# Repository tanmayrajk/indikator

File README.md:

# don't hit me (indikator)

## what is it

don't hit me is a project containing multiple tools/gadgets to aid us during biking. atm there's a handle bar with indicator lights in [the repo dont-hit-me](https://github.com/istoocold/dont-hit-me) and an actual indicator for the seat in this repo. 

there's plans for more stuff like phone holder, some sort of communication between bikes and other stuff maybe.

## features

- indicators on the handle bar that will tell you where your partner is moving.
- indicators for the seat that will allow others to see where you are moving.
- buttons on the handle bar to use the indicator lights.
- using espnow to communicate between the handle bar and the indicators AND the bikes.

## repos

it's currently divided between two repos:
- indikator (this repo)
- dont-hit-me ([https://github.com/istoocold/dont-hit-me](https://github.com/istoocold/dont-hit-me))

## installation

there's no installation needed tbh. just close the repo and open it with kicad. same for the dont-hit-me repo. use freecad for the cad stuff.

## ai usage

we just used chatgpt for asking questions. ai was not used for generating any code or images, etc.

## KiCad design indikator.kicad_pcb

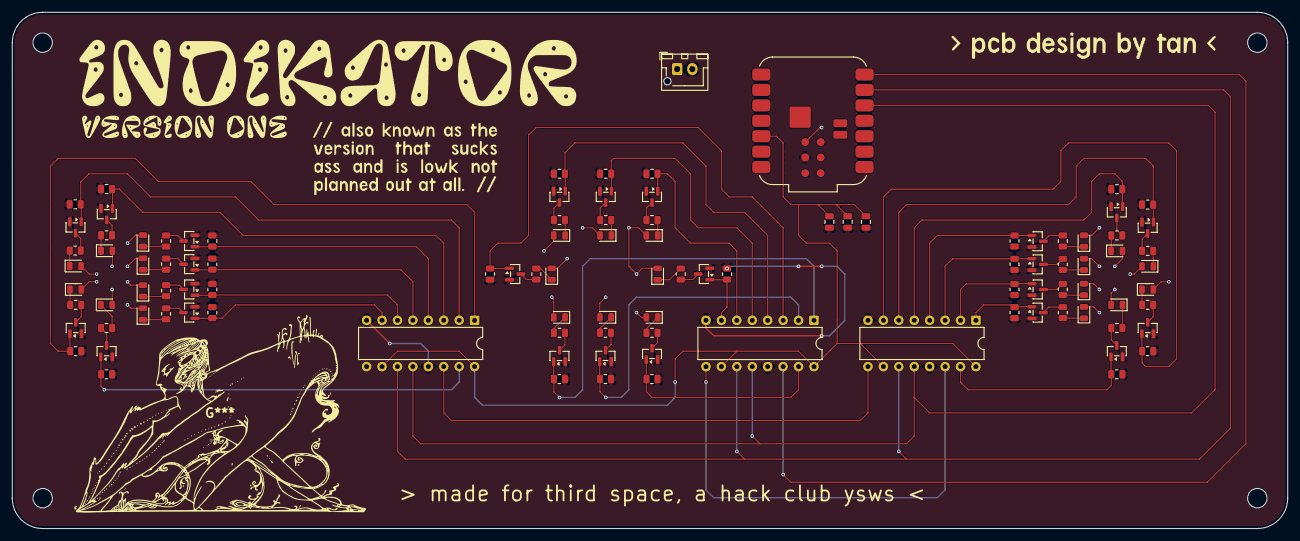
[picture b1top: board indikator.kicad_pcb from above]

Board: 2 copper layers, 210.0 x 85.0 mm, 104 parts (0 on the bottom side), 80 nets.

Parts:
C1, C2, C3: C; C_0805_2012Metric
D1, D2, D3, D4, D5, D6, D7, D8, D9, D10, D11, D12, D13, D14, D15, D16, D17, D18, D19, D20, D21, D22, D23, D24: LED; LED_0805_2012Metric
J1: Conn_01x02; JST_XH_B2B-XH-AM_1x02_P2.50mm_Vertical
Q1, Q2, Q3, Q4, Q5, Q6, Q7, Q8, Q9, Q10, Q11, Q12, Q13, Q14, Q15, Q16, Q17, Q18, Q19, Q20, Q21, Q22, Q23, Q24: AO3400A; SOT-23
R1, R2, R3, R4, R5, R6, R7, R8, R9, R10, R11, R12, R13, R14, R15, R16, R17, R18, R19, R20, R21, R22, R23, R24, R25, R26, R27, R28, R29, R30, R31, R32, R33, R34, R35, R36, R37, R38, R39, R40, R41, R42, R43, R44, R45, R46, R47, R48: R; R_0805_2012Metric
U1: XIAO-ESP32-C3-SMD; MCU_Seeed_ESP32C3
U2, U3, U4: 74HC595; DIP-16_W7.62mm

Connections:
/ESP3V3: C1.1, C2.1, C3.1, U1.12 (3V3_OUT), U2.10 (~SRCLR), U2.16 (VCC), U3.10 (~SRCLR), U3.16 (VCC), U4.10 (~SRCLR), U4.16 (VCC)
/QH'1: U2.9 (QH'), U3.14 (SER)
/QH'2: U3.9 (QH'), U4.14 (SER)
/RCLK: U1.5 (D4), U2.12 (RCLK), U3.12 (RCLK), U4.12 (RCLK)
/SER: U1.7 (D6), U2.14 (SER)
/SRCLK: U1.6 (D5), U2.11 (SRCLK), U3.11 (SRCLK), U4.11 (SRCLK)
/VBAT+: D1.2 (A), D2.2 (A), D3.2 (A), D4.2 (A), D5.2 (A), D6.2 (A), D7.2 (A), D8.2 (A), D9.2 (A), D10.2 (A), D11.2 (A), D12.2 (A), D13.2 (A), D14.2 (A), D15.2 (A), D16.2 (A), D17.2 (A), D18.2 (A), D19.2 (A), D20.2 (A), D21.2 (A), D22.2 (A), D23.2 (A), D24.2 (A), J1.1, U1.21 (VBAT)
GND: C1.2, C2.2, C3.2, J1.2, Q1.2 (S), Q2.2 (S), Q3.2 (S), Q4.2 (S), Q5.2 (S), Q6.2 (S), Q7.2 (S), Q8.2 (S), Q9.2 (S), Q10.2 (S), Q11.2 (S), Q12.2 (S), Q13.2 (S), Q14.2 (S), Q15.2 (S), Q16.2 (S), Q17.2 (S), Q18.2 (S), Q19.2 (S), Q20.2 (S), Q21.2 (S), Q22.2 (S), Q23.2 (S), Q24.2 (S), R1.2, R3.2, R5.2, R6.2, R7.2, R8.2, R9.2, R10.2, R17.2, R18.2, R19.2, R20.2, R21.2, R22.2, R23.2, R24.2, R33.2, R34.2, R35.2, R36.2, R37.2, R38.2, R39.2, R40.2, U1.22 (GND), U2.8 (GND), U2.13 (~OE), U3.8 (GND), U3.13 (~OE), U4.8 (GND), U4.13 (~OE)
unnamed: D1.1 (K), R2.2
unnamed: D2.1 (K), R4.2
unnamed: D3.1 (K), R11.2
unnamed: D4.1 (K), R12.2
unnamed: D5.1 (K), R13.2
unnamed: D6.1 (K), R14.2
unnamed: D7.1 (K), R15.2
unnamed: D8.1 (K), R16.2
unnamed: D9.1 (K), R25.2
unnamed: D10.1 (K), R26.2
unnamed: D11.1 (K), R27.2
unnamed: D12.1 (K), R28.2
unnamed: D13.1 (K), R29.2
unnamed: D14.1 (K), R30.2
unnamed: D15.1 (K), R31.2
unnamed: D16.1 (K), R32.2
unnamed: D17.1 (K), R41.2
unnamed: D18.1 (K), R42.2
unnamed: D19.1 (K), R43.2
unnamed: D20.1 (K), R44.2
unnamed: D21.1 (K), R45.2
unnamed: D22.1 (K), R46.2
unnamed: D23.1 (K), R47.2
unnamed: D24.1 (K), R48.2
unnamed: Q1.3 (D), R2.1
unnamed: Q1.1 (G), R1.1, U2.15 (QA)
unnamed: Q2.3 (D), R4.1
unnamed: Q2.1 (G), R3.1, U2.1 (QB)
unnamed: Q3.3 (D), R11.1
unnamed: Q3.1 (G), R5.1, U2.2 (QC)
unnamed: Q4.3 (D), R12.1
unnamed: Q4.1 (G), R6.1, U2.3 (QD)
unnamed: Q5.3 (D), R13.1
unnamed: Q5.1 (G), R7.1, U2.4 (QE)
unnamed: Q6.3 (D), R14.1
unnamed: Q6.1 (G), R8.1, U2.5 (QF)
unnamed: Q7.3 (D), R15.1
unnamed: Q7.1 (G), R9.1, U2.6 (QG)
unnamed: Q8.3 (D), R16.1
unnamed: Q8.1 (G), R10.1, U2.7 (QH)
unnamed: Q9.3 (D), R25.1
unnamed: Q9.1 (G), R17.1, U3.15 (QA)
unnamed: Q10.3 (D), R26.1
unnamed: Q10.1 (G), R18.1, U3.1 (QB)
unnamed: Q11.3 (D), R27.1
unnamed: Q11.1 (G), R19.1, U3.2 (QC)
unnamed: Q12.3 (D), R28.1
unnamed: Q12.1 (G), R20.1, U3.3 (QD)
unnamed: Q13.3 (D), R29.1
unnamed: Q13.1 (G), R21.1, U3.4 (QE)
unnamed: Q14.3 (D), R30.1
unnamed: Q14.1 (G), R22.1, U3.5 (QF)
unnamed: Q15.3 (D), R31.1
unnamed: Q15.1 (G), R23.1, U3.6 (QG)
unnamed: Q16.3 (D), R32.1
unnamed: Q16.1 (G), R24.1, U3.7 (QH)
unnamed: Q17.3 (D), R41.1
unnamed: Q17.1 (G), R33.1, U4.15 (QA)
unnamed: Q18.3 (D), R42.1
unnamed: Q18.1 (G), R34.1, U4.1 (QB)
unnamed: Q19.3 (D), R43.1
unnamed: Q19.1 (G), R35.1, U4.2 (QC)
unnamed: Q20.3 (D), R44.1
unnamed: Q20.1 (G), R36.1, U4.3 (QD)
unnamed: Q21.3 (D), R45.1
unnamed: Q21.1 (G), R37.1, U4.4 (QE)
unnamed: Q22.3 (D), R46.1
unnamed: Q22.1 (G), R38.1, U4.5 (QF)
unnamed: Q23.3 (D), R47.1
unnamed: Q23.1 (G), R39.1, U4.6 (QG)
unnamed: Q24.3 (D), R48.1
unnamed: Q24.1 (G), R40.1, U4.7 (QH)

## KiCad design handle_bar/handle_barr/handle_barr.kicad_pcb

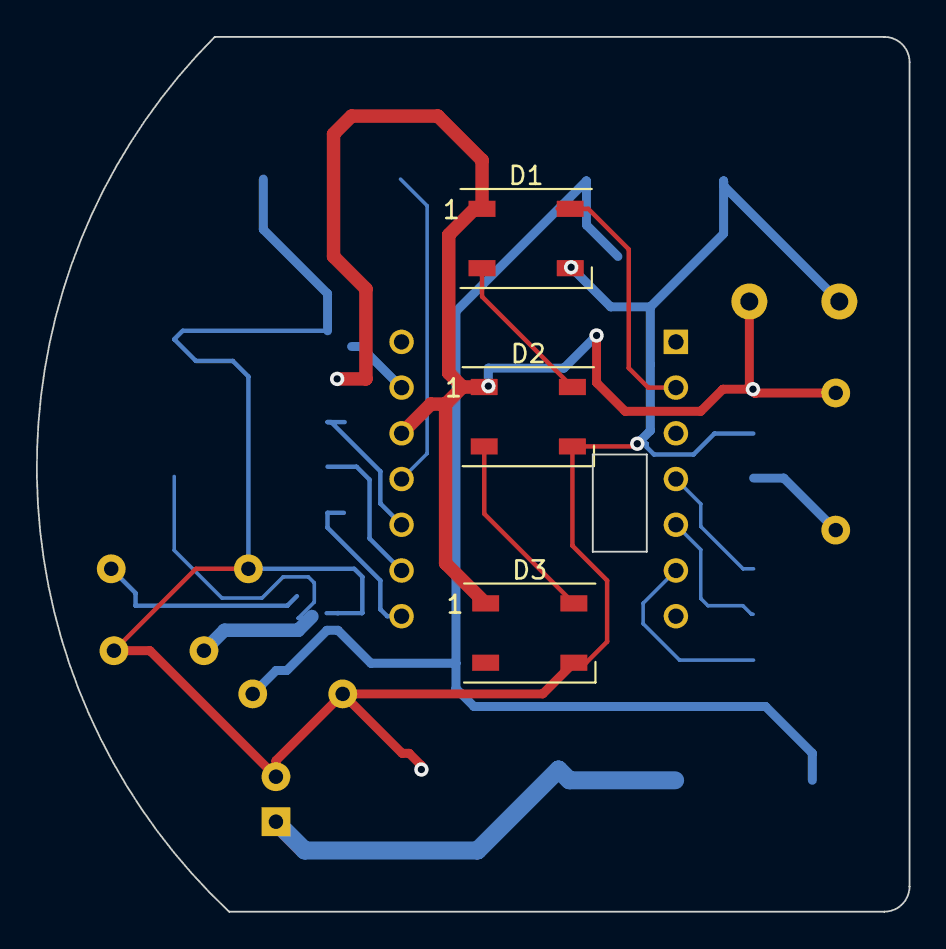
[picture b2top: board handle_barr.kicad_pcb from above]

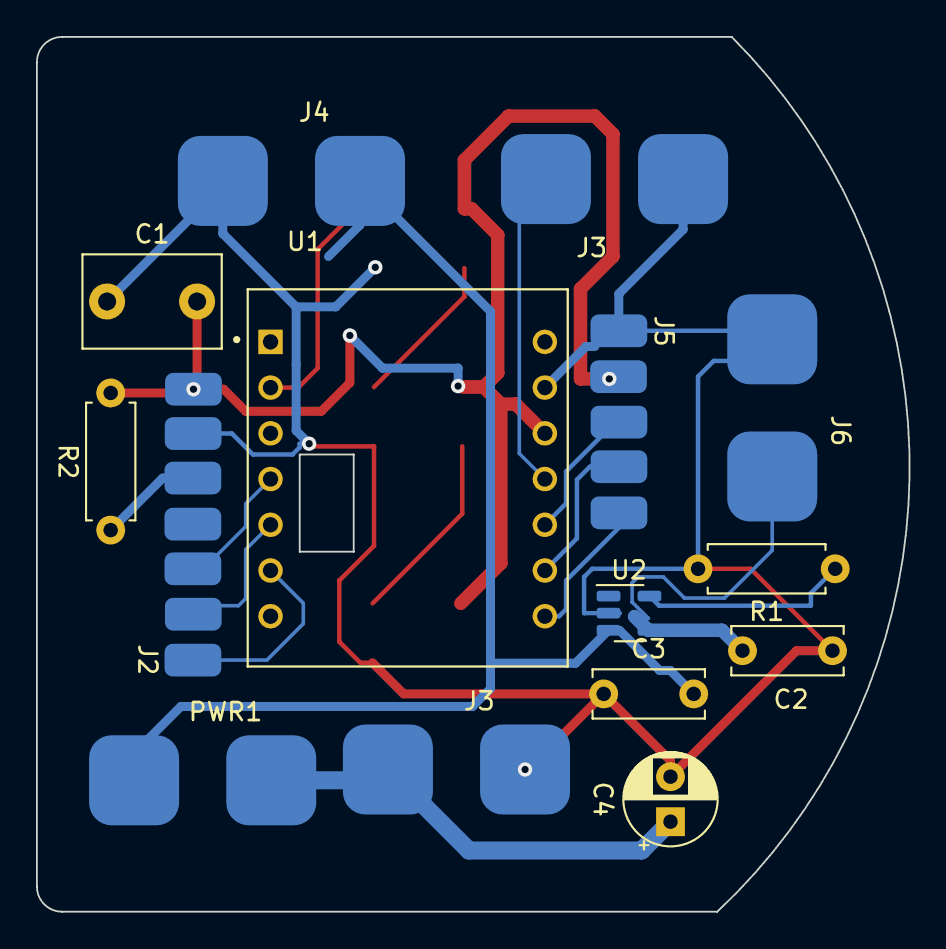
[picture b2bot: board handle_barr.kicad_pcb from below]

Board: 2 copper layers, 48.5 x 48.6 mm, 18 parts (15 on the bottom side), 17 nets.

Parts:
C1: 10uf; C_Disc_D7.5mm_W5.0mm_P5.00mm
C2, C3: 4.7; C_Disc_D6.0mm_W2.5mm_P5.00mm
C4: 22uf; CP_Radial_D5.0mm_P2.50mm
D1, D2, D3: WS2812B; LED_WS2812B_PLCC4_5.0x5.0mm_P3.2mm
J2: MAX98357A 3V3; SolderWirePad_1x07_SMD_1x3mm
J3: PWR_SLIDE; SolderWirePad_1x02_SMD_5x5mm
J3#2: HRN_SW; SolderWirePad_1x02_SMD_5x5mm
J4: BAT; SolderWirePad_1x02_SMD_5x5mm
J5: PS2; SolderWirePad_1x05_SMD_1x3mm
J6: USB; SolderWirePad_1x02_SMD_5x5mm
PWR1: SW_SPST; SolderWirePad_1x02_SMD_5x5mm
R1: 2kΩ; R_Axial_DIN0207_L6.3mm_D2.5mm_P7.62mm_Horizontal
R2: 220ko; R_Axial_DIN0207_L6.3mm_D2.5mm_P7.62mm_Horizontal
U1: XIAO_ESP32C3; MODULE_XIAO_ESP32C3
U2: MCP73831-2-OT; SOT-23-5

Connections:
3V3: C1.2, D1.1 (VDD), D2.1 (VDD), D3.1 (VDD), J2.7, J5.2, R2.2, U1.12 (VCC_3V3)
BAT_RAW: C3.2, J4.1, PWR1.2 (B), U2.3 (VBAT)
BAT_SYS: C4.1, J3.2, PWR1.1 (A)
BCLK: J2.2, U1.5 (D4)
DIN: J2.3, U1.4 (D3)
GND: C1.1, C2.2, C3.1, C4.2, D1.3 (VSS), D2.3 (VSS), D3.3 (VSS), J2.6, J3.1, J3#2.2, J4.2, J5.1, J6.2, R1.2, U1.13 (GND), U2.2 (VSS)
HORN: J3#2.1, U1.11 (D10)
LED_DIN: D1.4 (DIN), U1.2 (D1)
LRCLK: J2.1, U1.6 (D5)
unnamed: D1.2 (DOUT), D2.4 (DIN)
unnamed: D2.2 (DOUT), D3.4 (DIN)
unnamed: R1.1, U2.5 (PROG)
SD: J2.5, R2.1
SW_JS: J5.5, U1.8 (RX_D7)
VDD: C2.1, J6.1, U2.4 (VDD)
VRx: J5.3, U1.10 (D9)
VRy: J5.4, U1.9 (D8)
